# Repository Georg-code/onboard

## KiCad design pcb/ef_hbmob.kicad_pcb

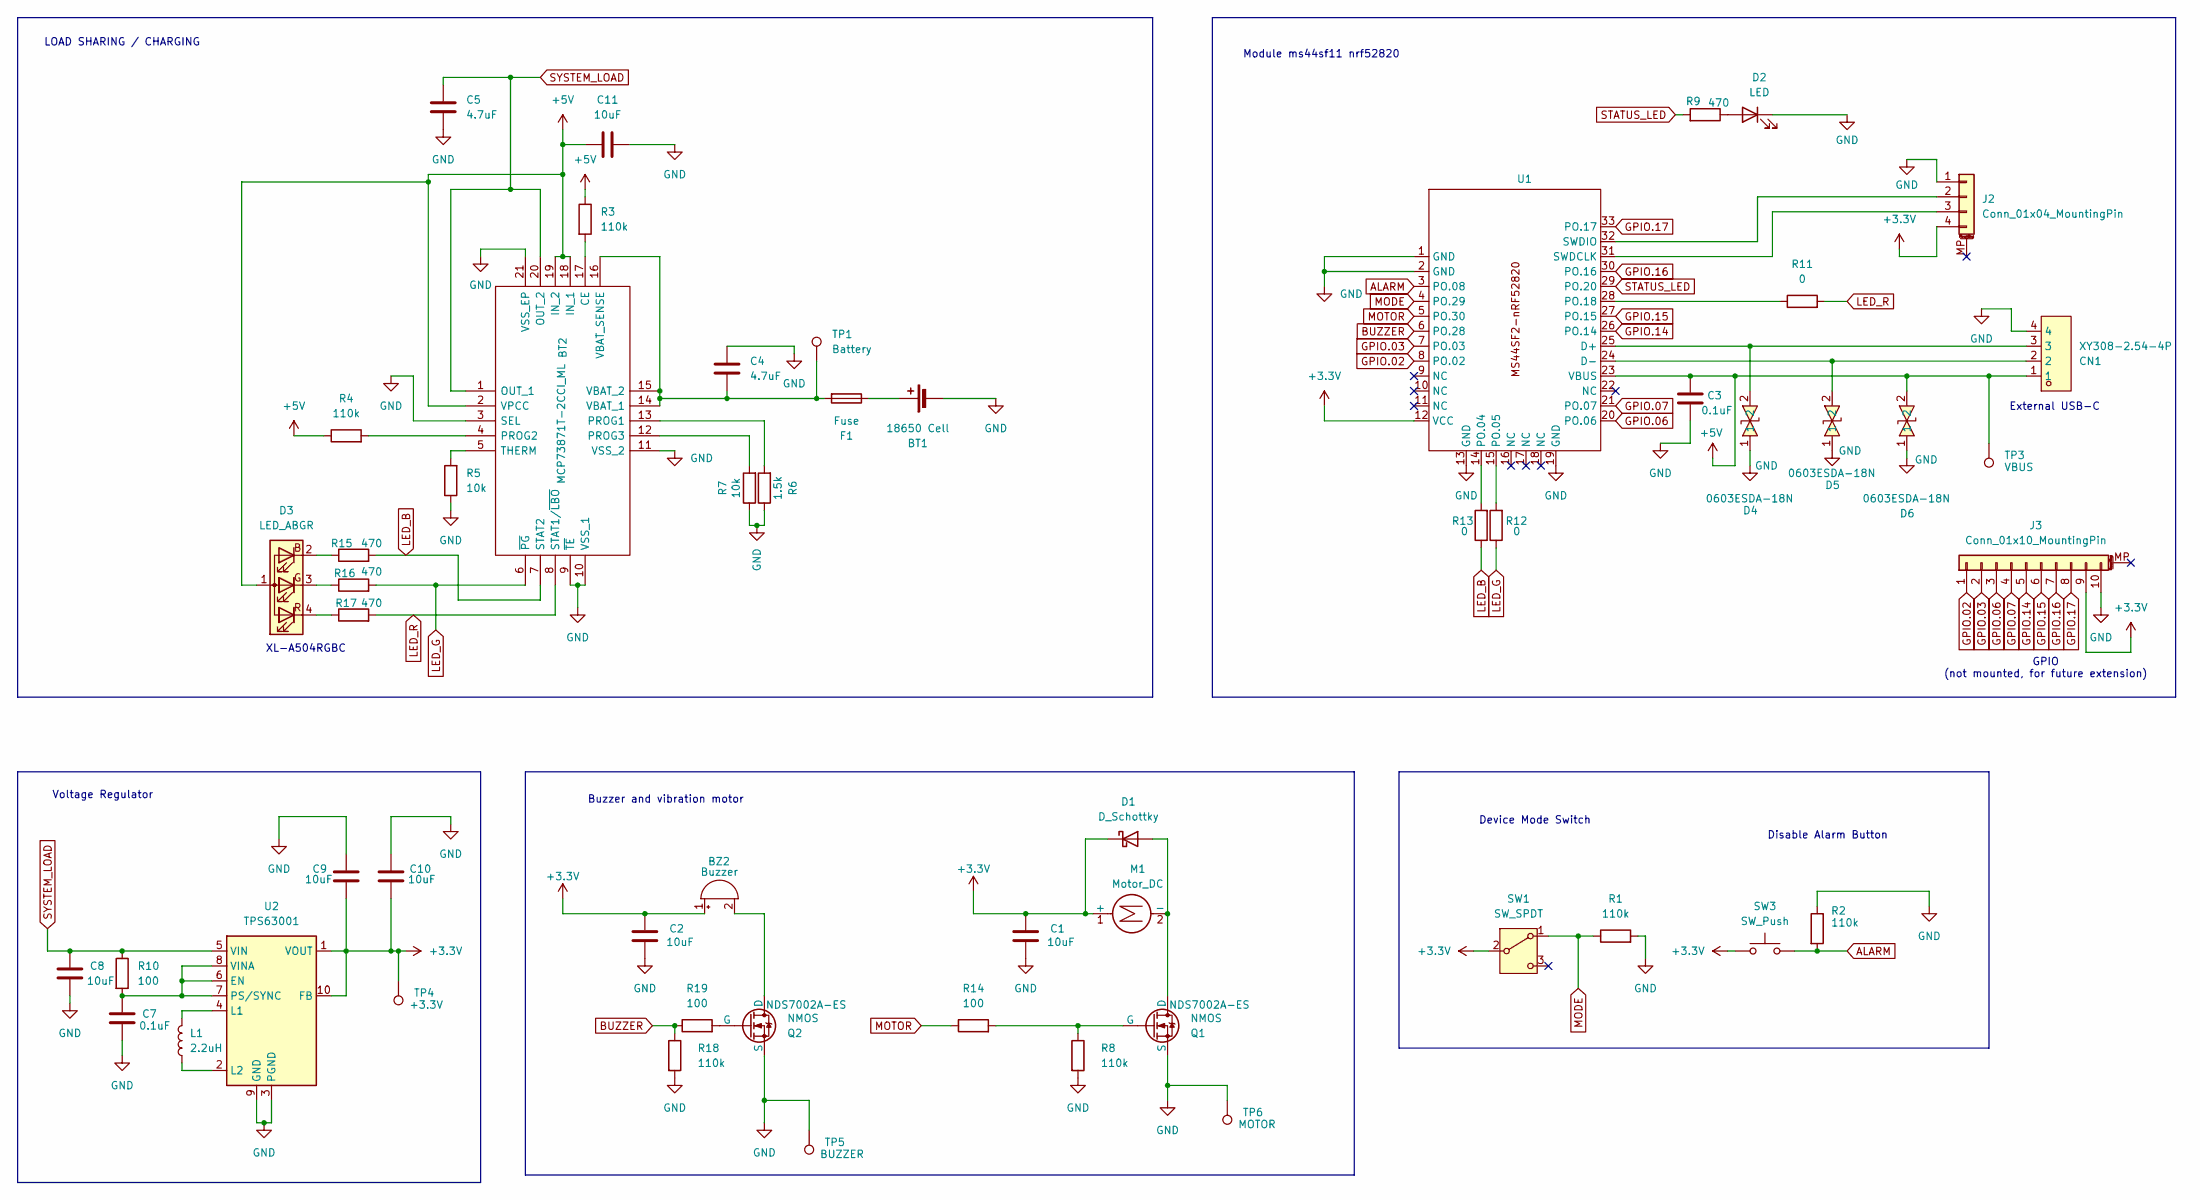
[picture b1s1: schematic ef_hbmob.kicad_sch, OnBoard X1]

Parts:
BT1: 18650 Cell; BAT-TH_BH-18650-A1AJ005
BT2: MCP73871T-2CCI_ML; QFN-20_L4.0-W4.0-P0.5-BL-EP; Manufacturer_Part_Number MCP73871T-2CCI/ML; Mouser Part Number 579-MCP73871T2CCIML
BZ2: Buzzer; BUZ-TH_BD9.0-P5.00-D0.6-FD
C1, C2, C8, C9, C10, C11: 10uF; C1206
C3, C7: 0.1uF; C1206
C4, C5: 4.7uF; C1206
CN1: XY308-2.54-4P; CONN-TH_XY308-2.54-4P; LCSC Part C915913
D1: D_Schottky; DIO-SMD_L3.4-W1.9-RD
D2: LED; LED1206-RD; LCSC C84273
D3: LED_ABGR; LED-TH_4P-BD5.8-P1.25_DM-50346EH-73826CC-05RGB-BML60-D; LCSC C7371894
D4, D5, D6: 0603ESDA-18N; D0603-BI; LCSC Part C316055
F1: Fuse; F1206; LCSC C207041
J2: Conn_01x04_MountingPin; HDR-TH_4P-P2.54-V-M
J3: Conn_01x10_MountingPin; HDR-TH_10P-P2.54-V-M
L1: 2.2uH; IND-SMD_L3.0-W3.0_NR3010
M1: Motor_DC; CONN-TH_DB301V-3.5-2P-GN
Q1, Q2: NMOS; SOT-23-3_L3.0-W1.6-P1.90-LS2.8-BR; LCSC C8545
R1, R2, R3, R4, R8, R18: 110k; R1206
R5, R7: 10k; R1206
R6: 1.5k; R1206
R9, R15, R16, R17: 470; R1206
R10: 100; R1206
R11, R12, R13: 0; R1206
R14, R19: 100; R_1206_3216Metric_Pad1.30x1.75mm_HandSolder
SW1: SW_SPDT; SW-TH_SHOU-HAN_SS12D10G4
SW3: SW_Push; KEY-TH_4P-L12.0-W12.0-P5.00-LS13.4-EH
TP1: Battery; TestPoint_Pad_D2.0mm
TP3: VBUS; TestPoint_Pad_D2.0mm
TP4: +3.3V; TestPoint_Pad_D2.0mm
TP5: BUZZER; TestPoint_Pad_D2.0mm
TP6: MOTOR; TestPoint_Pad_D2.0mm
U1: MS44SF1_V1.0
U2: TPS63001; Texas_DRC0010J_ThermalVias

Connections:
+3.3V: BZ2.1 (+), C1.2, C2.2, C9.2, C10.2, D1.1 (K), J2.4, J3.9, M1.1 (+), SW1.2 (B), SW3.1, TP4.1, U1.12 (VCC), U2.1 (VOUT), U2.10 (FB); also elsewhere on the board
+5V: BT2.2 (VPCC), BT2.18 (IN_1), BT2.19 (IN_2), C3.1, C11.1, CN1.1, D3.1 (A), D6.2, R3.1, R4.1, TP3.1, U1.23 (VBUS); also elsewhere on the board
ALARM: R2.2, SW3.2, U1.3 (PO.08)
BUZZER: R18.1, R19.1, U1.6 (PO.28)
GND: BT1.2 (-), BT2.3 (SEL), BT2.9 (~TE), BT2.10 (VSS_1), BT2.11 (VSS_2), BT2.21 (VSS_EP), C1.1, C2.1, C3.2, C4.1, C5.1, C7.2, C8.2, C9.1, C10.1, C11.2, CN1.4, D2.1 (K), D4.1, D5.1, D6.1, J2.1, J3.10, Q1.3 (S), Q2.3 (S), R1.2, R2.1, R5.1, R6.1, R7.1, R8.2, R18.2, TP5.1, TP6.1, U1.1 (GND), U1.2 (GND), U1.13 (GND), U1.19 (GND), U2.3 (PGND), U2.9 (GND), U2.11 (PGND); also elsewhere on the board
GPIO.02: J3.1, U1.8 (PO.02)
GPIO.03: J3.2, U1.7 (PO.03)
GPIO.06: J3.3, U1.20 (PO.06)
GPIO.07: J3.4, U1.21 (PO.07)
GPIO.14: J3.5, U1.26 (PO.14)
GPIO.15: J3.6, U1.27 (PO.15)
GPIO.16: J3.7, U1.30 (PO.16)
GPIO.17: J3.8, U1.33 (PO.17)
LED_B: BT2.7 (STAT2), R13.1, R15.2
LED_G: BT2.6 (~PG), R12.1, R16.2
LED_R: BT2.8 (STAT1/~LBO), R11.2, R17.2
MODE: R1.1, SW1.1 (A), U1.4 (PO.29)
MOTOR: R14.1, U1.5 (PO.30)
unnamed: BT1.1 (+), F1.1
unnamed: BT2.17 (CE), R3.2
unnamed: BT2.13 (PROG1), R6.2
unnamed: BT2.4 (PROG2), R4.2
unnamed: BT2.12 (PROG3), R7.2
unnamed: BT2.5 (THERM), R5.2
unnamed: BT2.14 (VBAT_1), BT2.15 (VBAT_2), BT2.16 (VBAT_SENSE), C4.2, F1.2, TP1.1
unnamed: BZ2.2 (-), Q2.1 (D)
unnamed: D1.2 (A), M1.2 (-), Q1.1 (D)
unnamed: D2.2 (A), R9.1
unnamed: D3.2 (BK), R15.1
unnamed: D3.3 (GK), R16.1
unnamed: D3.4 (RK), R17.1
unnamed: J2.2, U1.32 (SWDIO)
unnamed: J2.3, U1.31 (SWDCLK)
unnamed: Q1.2 (G), R8.1, R14.2
unnamed: Q2.2 (G), R19.2
unnamed: CN1.3, D4.2, U1.25 (D+)
unnamed: CN1.2, D5.2, U1.24 (D-)
unnamed: R13.2, U1.14 (PO.04)
unnamed: R12.2, U1.15 (PO.05)
unnamed: R11.1, U1.28 (PO.18)
unnamed: C7.1, R10.2, U2.6 (EN), U2.7 (PS/SYNC), U2.8 (VINA)
unnamed: L1.2, U2.4 (L1)
unnamed: L1.1, U2.2 (L2)
STATUS_LED: R9.2, U1.29 (PO.20)
SYSTEM_LOAD: BT2.1 (OUT_1), BT2.20 (OUT_2), C5.2, C8.1, R10.1, U2.5 (VIN)

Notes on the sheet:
External USB-C
XL-A504RGBC
GPIO (not mounted, for future extension)
Module ms44sf11 nrf52820
Disable Alarm Button
LOAD SHARING / CHARGING
Device Mode Switch
Voltage Regulator
Buzzer and vibration motor

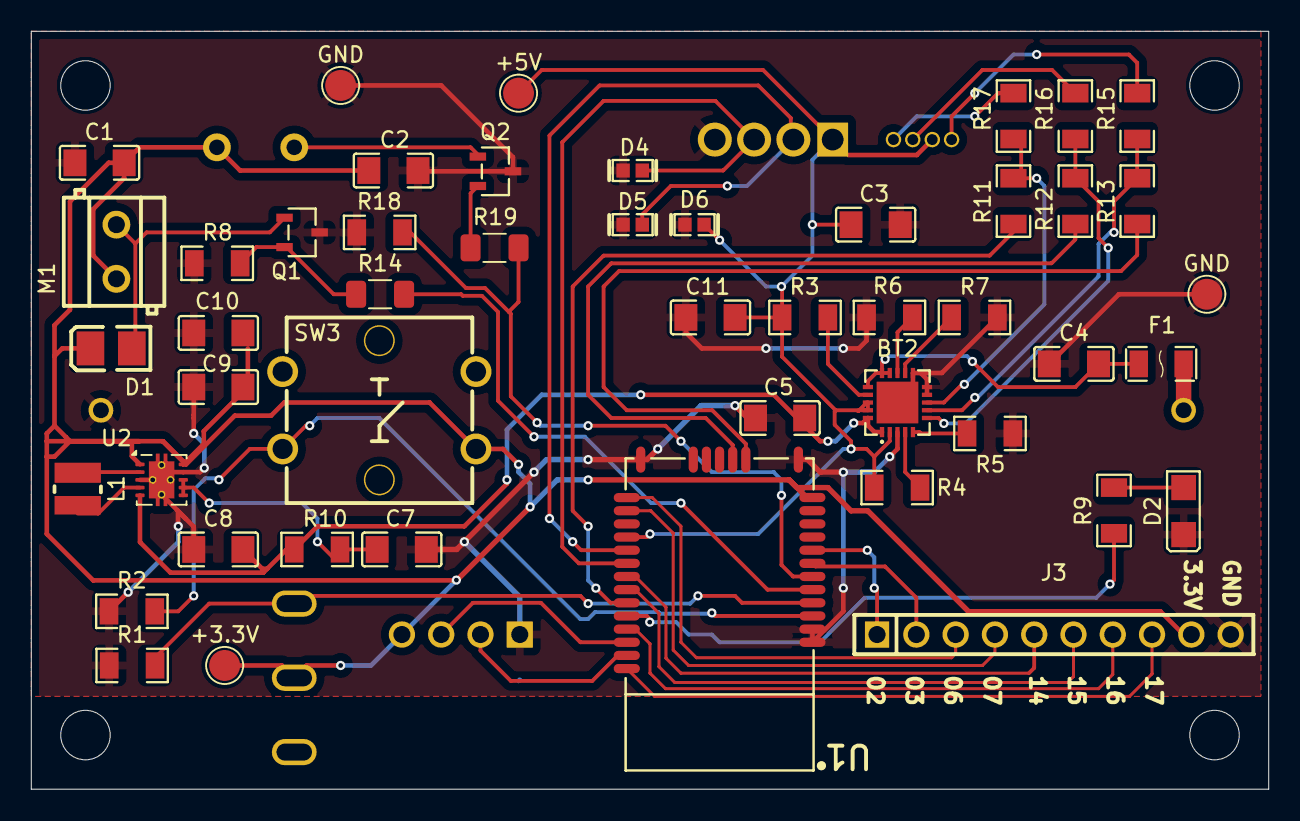
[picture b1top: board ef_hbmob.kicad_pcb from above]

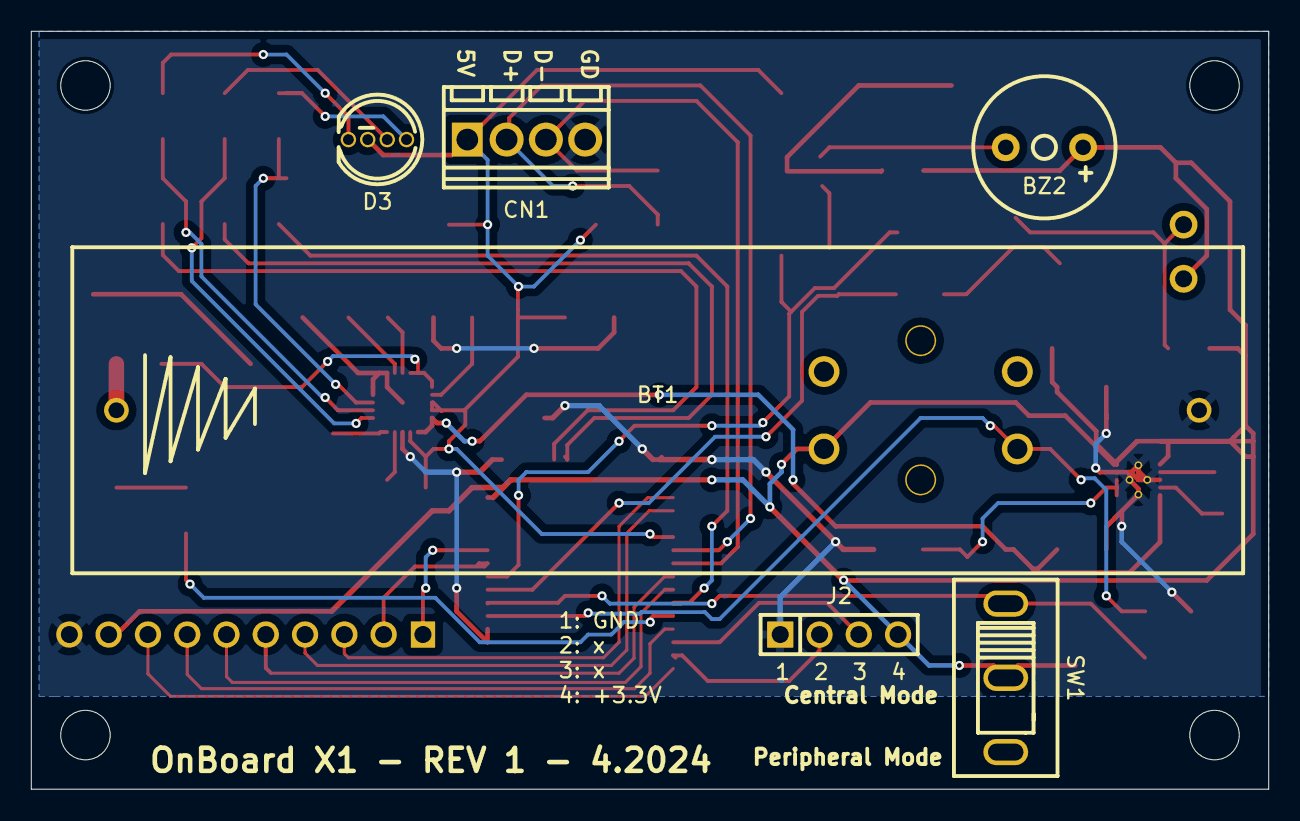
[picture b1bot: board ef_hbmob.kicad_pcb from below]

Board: 2 copper layers, 80.0 x 49.0 mm, 54 parts (6 on the bottom side), 45 nets.

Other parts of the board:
+3.3V: +3.3V; TestPoint_Pad_D2.0mm
+5V: VBUS; TestPoint_Pad_D2.0mm
GND: BUZZER; TestPoint_Pad_D2.0mm
GND#2: MOTOR; TestPoint_Pad_D2.0mm

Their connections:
+3.3V: +3.3V.1; also elsewhere on the board
+5V: +5V.1; also elsewhere on the board
GND: GND.1, GND#2.1; also elsewhere on the board

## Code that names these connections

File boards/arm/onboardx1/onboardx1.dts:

// Copyright (c) 2024 Nordic Semiconductor ASA
// SPDX-License-Identifier: Apache-2.0

/dts-v1/;
#include <nordic/nrf52820_qdaa.dtsi>
#include <zephyr/dt-bindings/gpio/gpio.h>



/ {
	model = "OnBoardX1";
	compatible = "georg-niggli,onboardx1";

	chosen {
		zephyr,sram = &sram0;
		zephyr,flash = &flash0;
		zephyr,code-partition = &slot0_partition;
	};








/* 

	zephyr,user {
		buzzer-gpios = <&gpioa 28 GPIO_ACTIVE_HIGH>;
		motor-gpios = <&gpioa 30 GPIO_ACTIVE_HIGH>;
	};
*/
	leds {
		compatible = "gpio-leds";
		status {
			label = "status";
			gpios = <&gpio0 20 0>;
		};
		motor {
			label = "motor";
			gpios = <&gpio0 30 0>;
		};
		buzzer {
			label = "buzzer";
			gpios = <&gpio0 28 0>;
		};
	};

	buttons {
		compatible = "gpio-keys";
		alarm {
			label = "alarm";
			gpios = <&gpio0 8 0>;
		};
	};


	


	aliases {
		albtn = &{/buttons/alarm/};
		stled = &{/leds/status/};
		moled = &{/leds/motor/};
		bzled = &{/leds/buzzer/};
	};

	
};

&flash0 {
	partitions {
		compatible = "fixed-partitions";
		#address-cells = <1>;
		#size-cells = <1>;

		boot_partition: partition@0 {
			label = "mcuboot";
			reg = <0x0 0xc000>;
		};
		slot0_partition: partition@c000 {
			label = "image-0";
			reg = <0xc000 0x12000>;
		};
		slot1_partition: partition@1e000 {
			label = "image-1";
			reg = <0x1e000 0x12000>;
		};
		scratch_partition: partition@30000 {
			label = "image-scratch";
			reg = <0x30000 0xa000>;
		};
		storage_partition: partition@3a000 {
			label = "storage";
			reg = <0x3a000 0x6000>;
		};
	};
};





&gpio0 {
	status = "okay";
};


&gpiote {
	status = "okay";
};

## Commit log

2024-05-07 Initial commit for onboard2
2024-05-07 (not so) basic configuration to get BLE working
2024-05-07 added custom Board
2024-05-07 added custom device and started gpio setup
2024-05-08 things start to work
2024-05-08 some things work, some things need fixes
2024-05-08 led works
2024-05-08 Create LICENSE
2024-05-08 more changes
2024-05-08 Great structual change + cad + pcb
2024-05-09 added central code
